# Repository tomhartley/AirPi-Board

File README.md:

AirPi-Board
===========

The board for the [AirPi](http://airpi.es/) weather station.

Both versions
-------------

Both versions have folowing sensors:
* BMP085 (temperature and air pressure)
* DHT22 (temperature and relative humidity)
* Electret microphone (sound levels)
* LDR (light levels)

Version 1.2
-----------

The PTH only board with MICS-2710 (measure nitrogen dioxide levels) and
MICS-5525 (measure carbon monoxide levels) sensors.

Version 1.4
-----------

The PTH board with MICS-4514 SMD sensor (measure carbon monoxide and nitrogen
dioxide levels).

Assembly
--------

Please refer to [AirPi Assembly Instructions](http://airpi.es/files/instructions/assembly.pdf).

Software
--------

The code is available at https://github.com/tomhartley/airpi

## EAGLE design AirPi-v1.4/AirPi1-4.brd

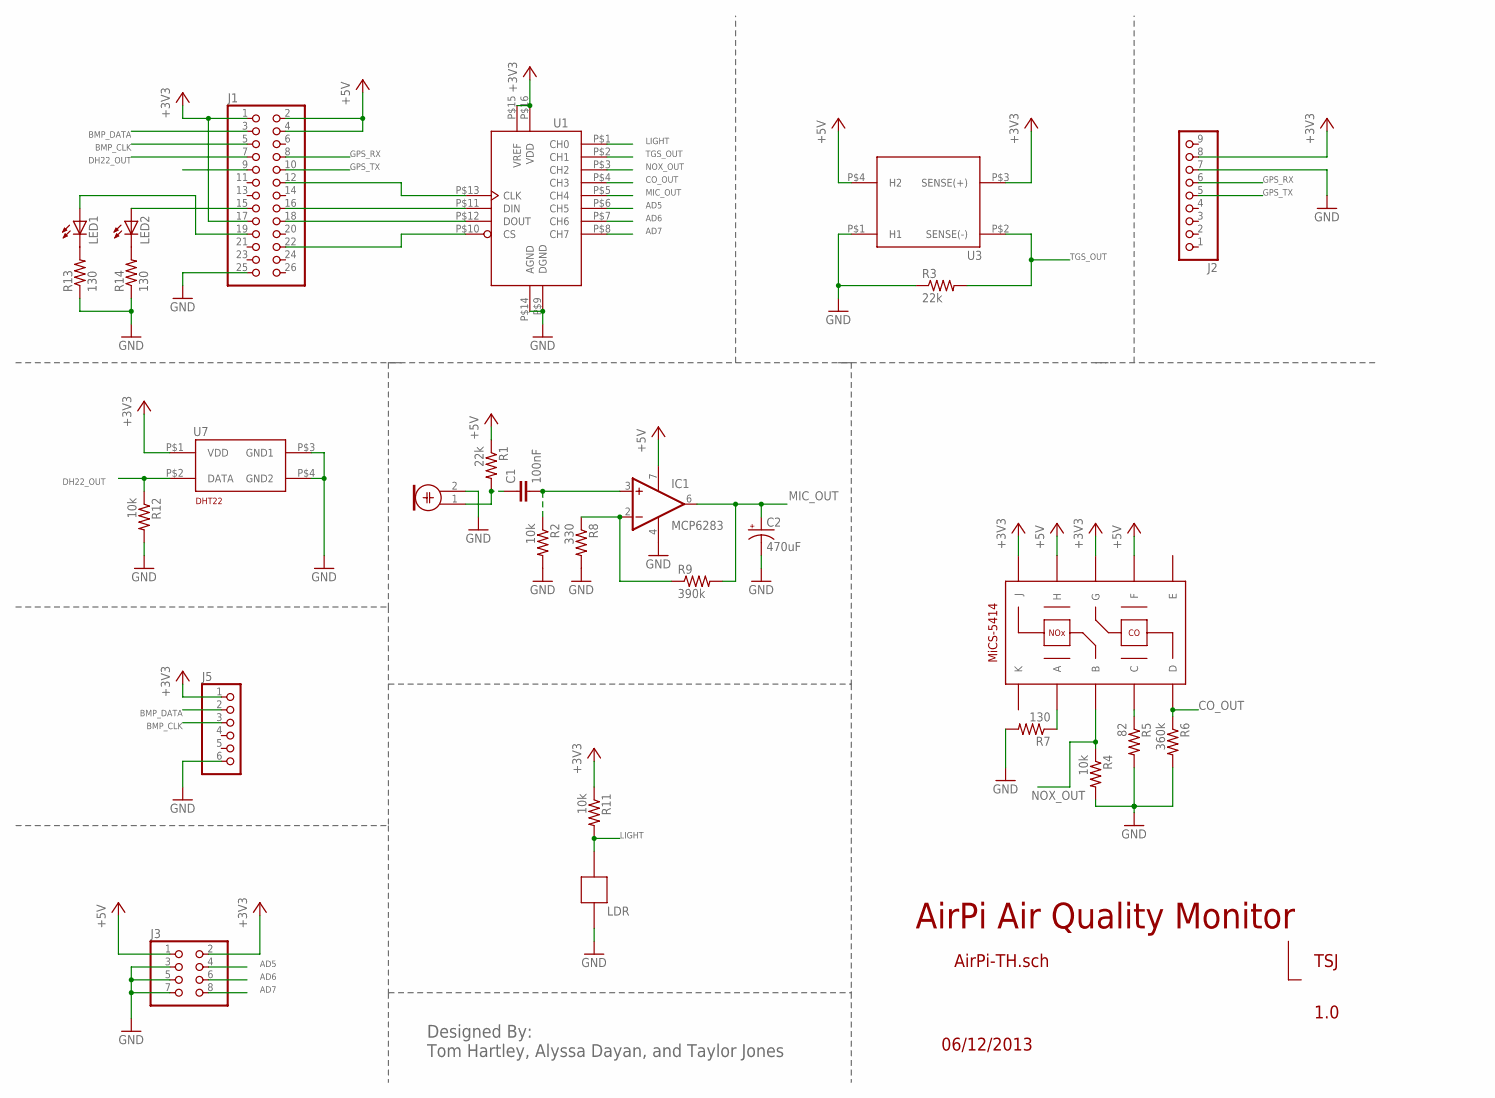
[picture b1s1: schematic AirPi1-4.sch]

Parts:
C1: 100nF; C2.5-4
C2: 470uF; E3,5-8
IC1: MCP6283; DIL08
IC2: MCP3008; DIL16
J1: PINHD-2X13; 2X13
J2: PINHD-1X9; 1X09-BIG
J3: PINHD-2X4; 2X04
J5: PINHD-1X6; 1X06
LDR1: LDR; LED5MM
LED1, LED2: LED3MM
M1: MIC; WM-62PC/62PK
MICS: MICS-4514
R1, R3: 22k; 0207/10
R2, R4, R11, R12: 10k; 0207/10
R5: 82; 0207/10
R6: 360k; 0207/10
R7, R13, R14: 130; 0207/10
R8: 330; 0207/10
R9: 390k; 0207/10
U3: TGS2600
U7: DHT22

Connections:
+3V3: IC2.P$15 (VREF), IC2.P$16 (VDD), J1.1, J1.17, J2.8, J3.2, J5.1, MICS.G, MICS.J, R11.1, U3.P$3 (SENSE(+)), U7.P$1 (VDD)
+5V: IC1.7 (V+), J1.2, J1.4, J3.1, MICS.F, MICS.H, R1.1, U3.P$4 (H2)
AD5: IC2.P$6 (CH5), J3.4
AD6: IC2.P$7 (CH6), J3.6
AD7: IC2.P$8 (CH7), J3.8
BMP_CLK: J1.5, J5.3
BMP_DATA: J1.3, J5.2
CO_OUT: IC2.P$4 (CH3), MICS.D, R6.1
DH22_OUT: J1.7, R12.1, U7.P$2 (DATA)
GND: C2.-, IC1.4 (V-), IC2.P$9 (DGND), IC2.P$14 (AGND), J1.25, J2.7, J3.3, J3.5, J3.7, J5.6, LDR1.K, M1.2, R2.2, R3.1, R4.2, R5.2, R6.2, R7.2, R8.2, R12.2, R13.1, R14.1, U3.P$1 (H1), U7.P$3 (GND1), U7.P$4 (GND2)
GPS_RX: J1.8, J2.6
GPS_TX: J1.10, J2.5
LIGHT: IC2.P$1 (CH0), LDR1.A, R11.2
MIC_OUT: C2.+, IC1.6 (OUT), IC2.P$5 (CH4), R9.2
unnamed: IC2.P$13 (CLK), J1.12
unnamed: IC2.P$12 (DOUT), J1.18
unnamed: IC2.P$10 (CS), J1.22
unnamed: IC2.P$11 (DIN), J1.16
unnamed: MICS.C, R5.1
unnamed: C1.1, M1.1, R1.2
unnamed: C1.2, IC1.3 (+IN), R2.1
unnamed: IC1.2 (-IN), R8.1, R9.1
unnamed: MICS.A, R7.1
unnamed: LED1.K (C), R13.2
unnamed: LED2.K (C), R14.2
unnamed: J1.19, LED1.A
unnamed: J1.15, LED2.A
NOX_OUT: IC2.P$3 (CH2), MICS.B, R4.1
TGS_OUT: IC2.P$2 (CH1), R3.2, U3.P$2 (SENSE(-))

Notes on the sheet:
AirPi Air Quality Monitor
1.0
06/12/2013
TSJ
AirPi-TH.sch
Designed By: Tom Hartley, Alyssa Dayan, and Taylor Jones
LDR

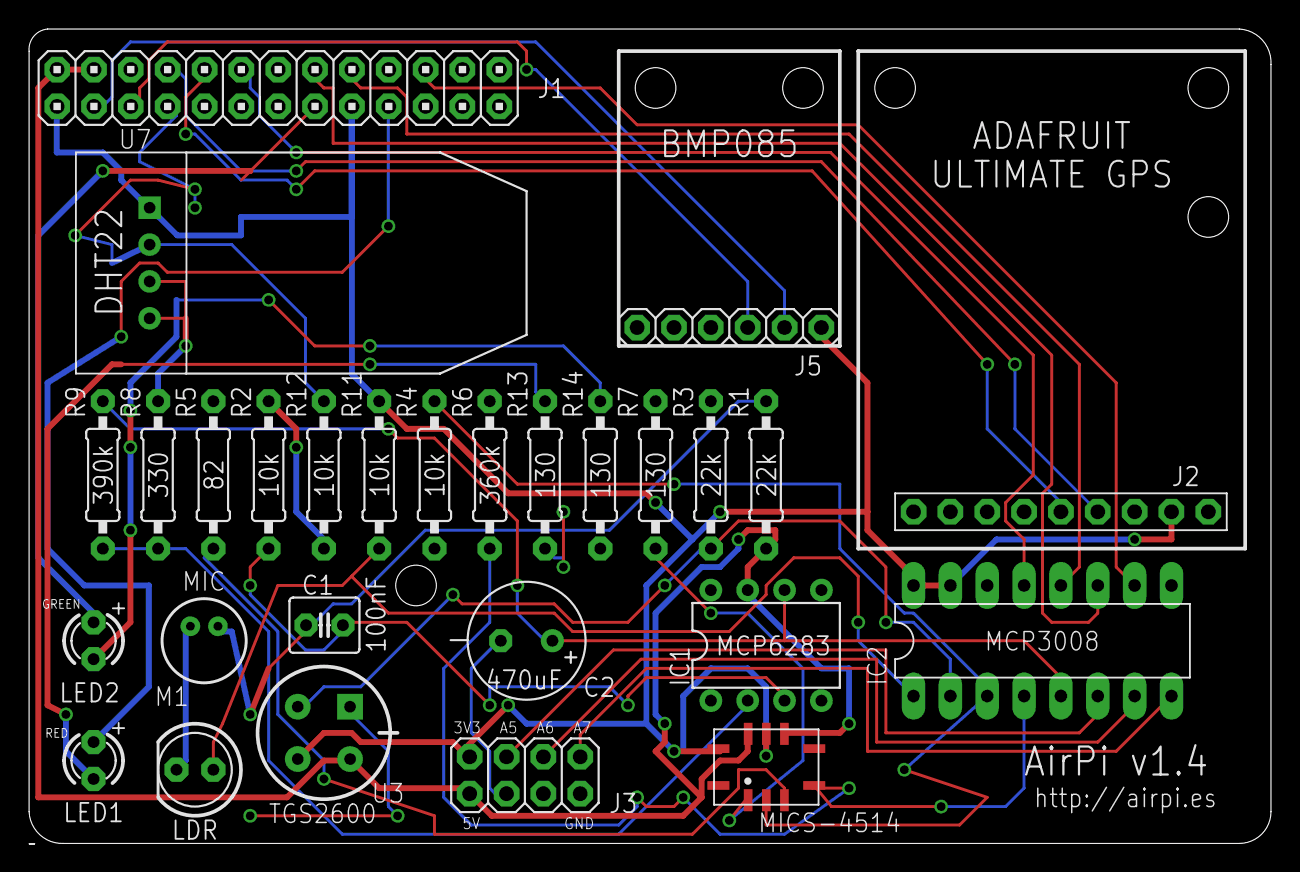
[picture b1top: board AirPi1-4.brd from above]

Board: 2 copper layers, 85.6 x 56.1 mm, 28 parts (0 on the bottom side), 29 nets.

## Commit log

2016-08-15 Renamed PTH/AirPi.* to AirPi-v1.2/AirPi1-2.* to make room for v1.4.
2016-08-15 Add AirPi Board version 1.4 (closes #1).
2016-08-15 Extended README.md to cover main difference between board v1.2 and v1.4.
